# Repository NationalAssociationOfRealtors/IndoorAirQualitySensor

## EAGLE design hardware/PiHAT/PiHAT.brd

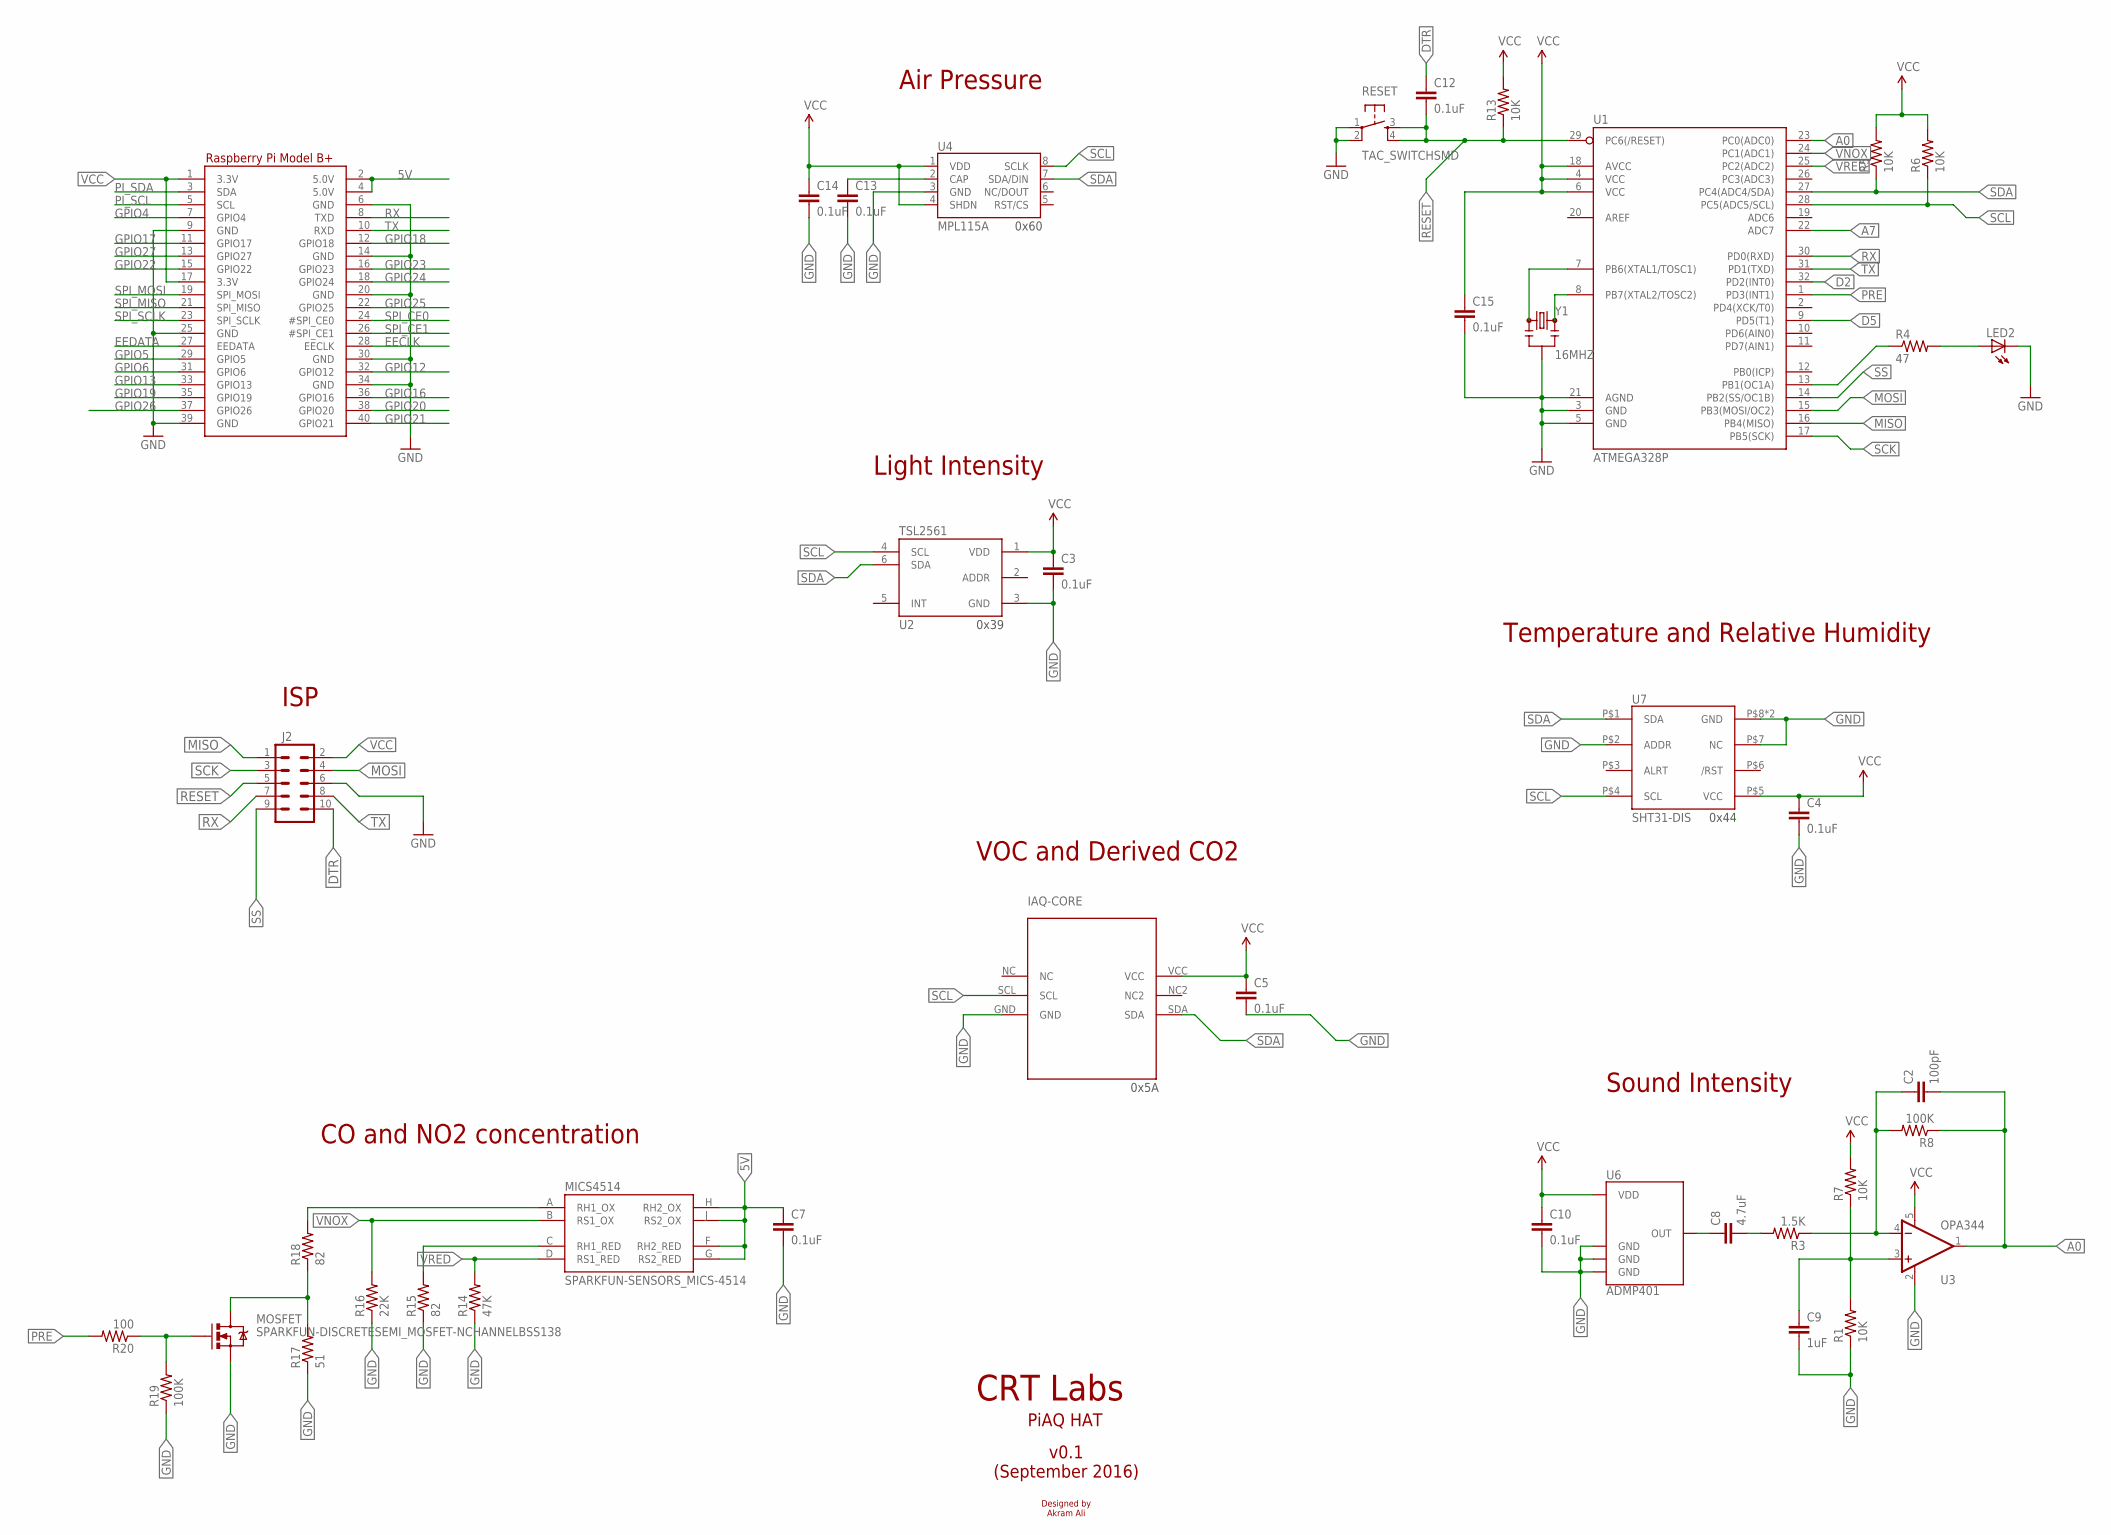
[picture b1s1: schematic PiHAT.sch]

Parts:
C2: 100pF; 0805; DIGIKEY# 311-1111-1-ND
C3, C4, C5, C7, C10, C12, C13, C14, C15: 0.1uF; 0805; DIGIKEY# 311-1088-1-ND
C8: 4.7uF; 0805; DIGIKEY# 311-1871-1-ND
C9: 1uF; 0805; DIGIKEY# 311-1365-1-ND
IAQ-CORE: IAQ-CORE; MPN IAQ CORE; DIGIKEY# IAQ-CORE C-ND
J2: M05X2PTH; AVR_ICSP; DIGIKEY# S6105-ND
LED2: LEDCHIPLED_0805; CHIPLED_0805; DIGIKEY# 475-1196-1-ND
MICS4514: SPARKFUN-SENSORS_MICS-4514; SPARKFUN-SENSORS_MICS_10-SMD
MOSFET: SPARKFUN-DISCRETESEMI_MOSFET-NCHANNELBSS138; SPARKFUN-DISCRETESEMI_SOT23-3
R1, R5, R6, R7, R13: 10K; 0805; DIGIKEY# 311-10KARCT-ND
R3: 1.5K; 0805; DIGIKEY# YAG1814CT-ND
R4: 47; 0805; DIGIKEY# 311-47ARCT-ND
R8: 100K; 0805; DIGIKEY# 541-82.0CCT-ND
R14: 47K; 0805; DIGIKEY# RHM47KKCT-ND
R15, R18: 82; 0805; DIGIKEY# 541-82.0CCT-ND
R16: 22K; 0805; DIGIKEY# 311-22KARCT-ND
R17: 51; 0805; DIGIKEY# RHM51KCT-ND
R19: 100K; 0805; DIGIKEY# 311-100KCRCT-ND
R20: 100; 0805; DIGIKEY# 311-100CRCT-ND
RESET: TAC_SWITCHSMD; TACTILE-SWITCH-SMD; DIGIKEY# CKN9104CT-ND
RPI1: RASPBERRYPI_BPLUS_HATSLOTS; PI_HAT_SLOTS
U1: ATMEGA328P; TQFP32-08; MPN ATMEGA328PB-AU; DIGIKEY# ATMEGA328P-AU-ND
U2: TSL2561; FN-6; MOUSER# 856-TSL2561T; DIGIKEY# TSL2561-FNCT-ND
U3: OPA344; SOT23-5; DIGIKEY# 296-41475-1-ND
U4: MPL115A; LGA8; DIGIKEY# MPL115A2-ND
U6: ADMP401; DIGIKEY# INMP401ACEZ-R7CT-ND
U7: SHT31-DIS; SHT3X; MPN SHT31-DIS-B; DIGIKEY# 1649-1011-1-ND
Y1: 16MHZ; RESONATOR-SMD; DIGIKEY# 490-1198-1-ND

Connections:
5V: C7.1, MICS4514.F (RH2_RED), MICS4514.G (RS2_RED), MICS4514.H (RH2_OX), MICS4514.J (RS2_OX), RPI1.2 (5.0V), RPI1.4 (5.0V)
A0: C2.2, R8.1, U1.23 (PC0(ADC0)), U3.1 (OUT)
A7: U1.22 (ADC7)
D2: U1.32 (PD2(INT0))
D5: U1.9 (PD5(T1))
DTR: C12.1, J2.10
EECLK: RPI1.28 (EECLK)
EEDATA: RPI1.27 (EEDATA)
GND: C3.2, C4.2, C5.2, C7.2, C9.2, C10.2, C13.2, C14.2, C15.2, IAQ-CORE.GND, J2.6, LED2.C, MOSFET.2 (S), R1.1, R14.1, R15.1, R16.1, R17.1, R19.1, RESET.1, RESET.2, RPI1.6 (GND), RPI1.9 (GND), RPI1.14 (GND), RPI1.20 (GND), RPI1.25 (GND), RPI1.30 (GND), RPI1.34 (GND), RPI1.39 (GND), U1.3 (GND), U1.5 (GND), U1.21 (AGND), U2.3 (GND), U3.2 (V-), U4.3 (GND), U6.2 (GND), U6.4 (GND), U6.6 (GND), U7.P$2 (ADDR), U7.P$7 (NC), U7.P$8 (GND), U7.PAD (GND), Y1.2
GPIO4: RPI1.7 (GPIO4)
GPIO5: RPI1.29 (GPIO5)
GPIO6: RPI1.31 (GPIO6)
GPIO12: RPI1.32 (GPIO12)
GPIO13: RPI1.33 (GPIO13)
GPIO16: RPI1.36 (GPIO16)
GPIO17: RPI1.11 (GPIO17)
GPIO18: RPI1.12 (GPIO18)
GPIO19: RPI1.35 (GPIO19)
GPIO20: RPI1.38 (GPIO20)
GPIO21: RPI1.40 (GPIO21)
GPIO22: RPI1.15 (GPIO22)
GPIO23: RPI1.16 (GPIO23)
GPIO24: RPI1.18 (GPIO24)
GPIO25: RPI1.22 (GPIO25)
GPIO26: RPI1.37 (GPIO26)
GPIO27: RPI1.13 (GPIO27)
MISO: J2.1, U1.16 (PB4(MISO))
MOSI: J2.4, U1.15 (PB3(MOSI/OC2))
unnamed: R4.1, U1.13 (PB1(OC1A))
unnamed: LED2.A, R4.2
unnamed: U1.8 (PB7(XTAL2/TOSC2)), Y1.3
unnamed: U1.7 (PB6(XTAL1/TOSC1)), Y1.1
unnamed: C8.1, U6.1 (OUT)
unnamed: MICS4514.A (RH1_OX), R18.2
unnamed: C8.2, R3.2
unnamed: C2.1, R3.1, R8.2, U3.4 (-IN)
unnamed: C9.1, R1.2, R7.1, U3.3 (+IN)
unnamed: C13.1, U4.2 (CAP)
unnamed: MICS4514.C (RH1_RED), R15.2
unnamed: MOSFET.3 (D), R17.2, R18.1
unnamed: MOSFET.1 (G), R19.2, R20.1
PI_SCL: RPI1.5 (SCL)
PI_SDA: RPI1.3 (SDA)
PRE: R20.2, U1.1 (PD3(INT1))
RESET: C12.2, J2.5, R13.1, RESET.3, RESET.4, U1.29 (PC6(/RESET))
RX: J2.7, RPI1.8 (TXD), U1.30 (PD0(RXD))
SCK: J2.3, U1.17 (PB5(SCK))
SCL: IAQ-CORE.SCL, R6.1, U1.28 (PC5(ADC5/SCL)), U2.4 (SCL), U4.8 (SCLK), U7.P$4 (SCL)
SDA: IAQ-CORE.SDA, R5.1, U1.27 (PC4(ADC4/SDA)), U2.6 (SDA), U4.7 (SDA/DIN), U7.P$1 (SDA)
SPI_CE0: RPI1.24 (#SPI_CE0)
SPI_CE1: RPI1.26 (#SPI_CE1)
SPI_MISO: RPI1.21 (SPI_MISO)
SPI_MOSI: RPI1.19 (SPI_MOSI)
SPI_SCLK: RPI1.23 (SPI_SCLK)
SS: J2.9, U1.14 (PB2(SS/OC1B))
TX: J2.8, RPI1.10 (RXD), U1.31 (PD1(TXD))
VCC: C3.1, C4.1, C5.1, C10.1, C14.1, C15.1, IAQ-CORE.VCC, J2.2, R5.2, R6.2, R7.2, R13.2, RPI1.1 (3.3V), RPI1.17 (3.3V), U1.4 (VCC), U1.6 (VCC), U1.18 (AVCC), U2.1 (VDD), U3.5 (V+), U4.1 (VDD), U4.4 (SHDN), U6.5 (VDD), U7.P$5 (VCC)
VNOX: MICS4514.B (RS1_OX), R16.2, U1.24 (PC1(ADC1))
VRED: MICS4514.D (RS1_RED), R14.2, U1.25 (PC2(ADC2))

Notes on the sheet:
Light Intensity
VOC and Derived CO2
Air Pressure
Sound Intensity
Temperature and Relative Humidity
ISP
CO and NO2 concentration
CRT Labs
PiAQ HAT
v0.1 (September 2016)
Designed by Akram Ali
0x39
0x60
0x5A
0x44

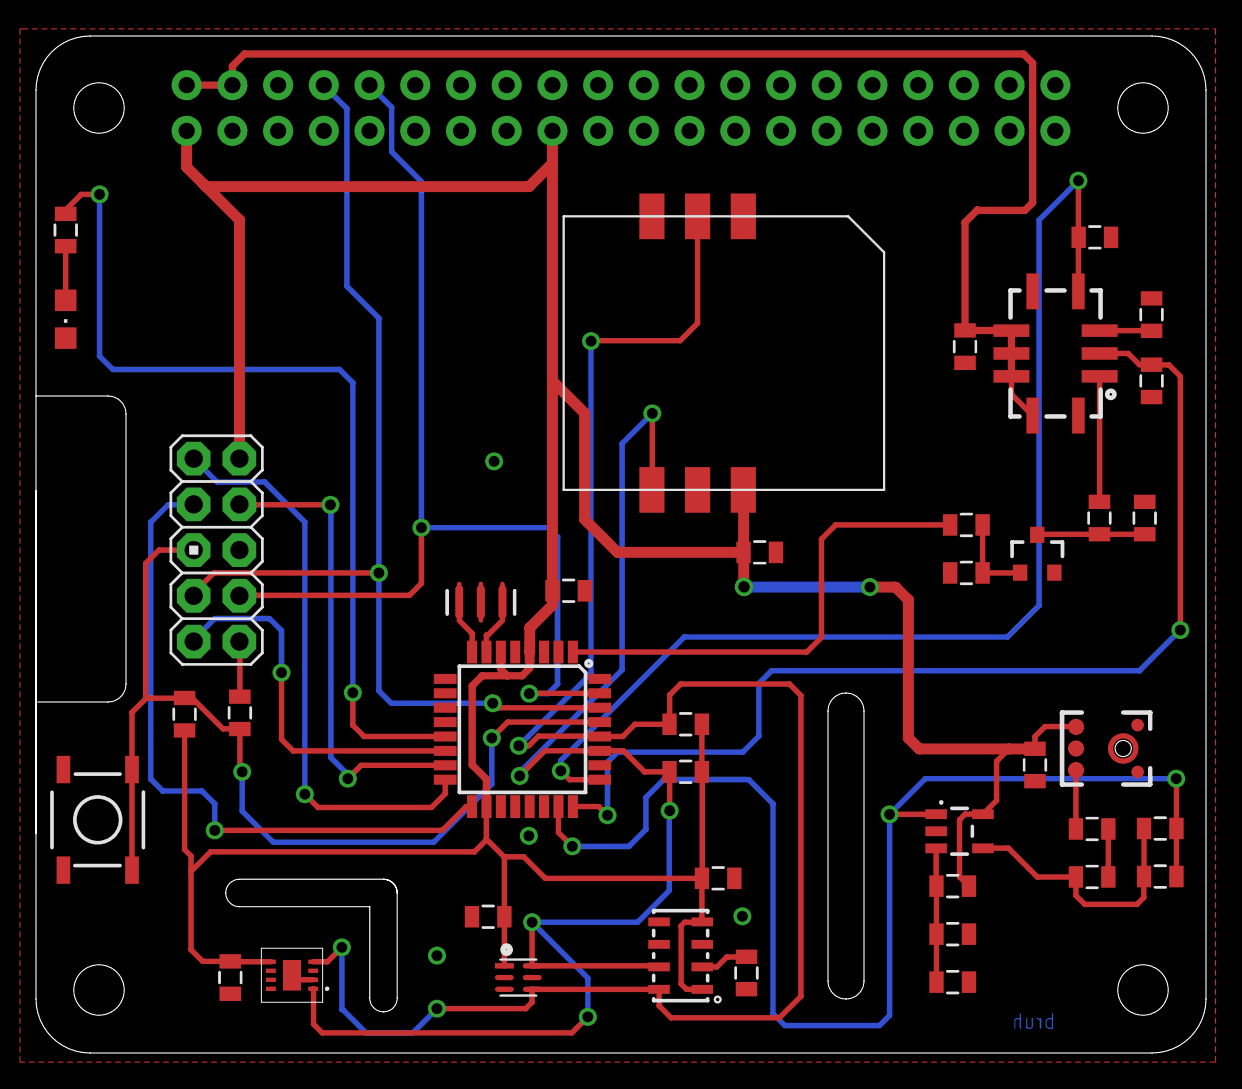
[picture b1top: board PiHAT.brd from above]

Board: 2 copper layers, 65.0 x 56.5 mm, 41 parts (0 on the bottom side), 30 nets.

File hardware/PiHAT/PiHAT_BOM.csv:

Qty,Value,Device,Package,Parts,Description,DIGIKEY#,MANF,MANF#,MF,MOUSER#,MPN,OC_NEWARK,PROD_ID,VALUE
1,,LEDCHIPLED_0805,CHIPLED_0805,LED2,LED,475-1196-1-ND,,,,,,unknown,,
1,,M05X2PTH,AVR_ICSP,J2,Header 5x2,,,,,,,,,
9,0.1uF,CAP0805,805,C3,,311-1088-1-ND,,,,,,,,
1,1.5K,RESISTOR0805-RES,805,R3,Resistor,YAG1814CT-ND,,,,,,,,
1,100,RESISTOR0805-RES,805,R20,Resistor,311-100CRCT-ND,,,,,,,,
1,100K,RESISTOR0805-RES,805,R19,Resistor,311-100KCRCT-ND,,,,,,,,
1,100K,RESISTOR0805-RES,805,R8,Resistor,541-82.0CCT-ND,,,,,,,,
1,100pF,CAP0805,805,C2,Capacitor,311-1111-1-ND,,,,,,,,
5,10K,RESISTOR0805-RES,805,R1,,,,,,,,,,
1,16MHZ,RESONATOR16MHZ,RESONATOR-SMD,Y1,Resonator,490-1198-1-ND,,,,,,unknown,XTAL-08900,16MHZ
1,1uF,CAP0805,805,C9,Capacitor,311-1365-1-ND,,,,,,,,
1,22K,RESISTOR0805-RES,805,R16,Resistor,311-22KARCT-ND,,,,,,unknown,,
1,4.7uF,CAP0805,805,C8,Capacitor,311-1871-1-ND,,,,,,,,
1,47,RESISTOR0805-RES,805,R4,Resistor,311-47ARCT-ND,,,,,,unknown,,
1,47K,RESISTOR0805-RES,805,R14,Resistor,RHM47KKCT-ND,,,,,,unknown,,
1,51,RESISTOR0805-RES,805,R17,Resistor,RHM51KCT-ND,,,,,,,,
2,82,RESISTOR0805-RES,805,R15,,541-82.0CCT-ND,,,,,,,,
1,ADMP401,ADMP401,ADMP401,U6,Omnidirection bottom-port MEMS microphone,INMP401ACEZ-R7CT-ND,,,,,,,,
1,ATMEGA328P,ATMEGA328P_TQFP,TQFP32-08,U1,,ATMEGA328P-AU-ND,,,,,ATMEGA328PB-AU,58Y6083,IC-09069,ATMEGA328P_TQFP
1,IAQ-CORE,IAQ-CORE,IAQ-CORE,IAQ-CORE,,IAQ-CORE C-ND,,,,,IAQ CORE,82Y5455,,
1,MPL115A,MPL115A,LGA8,U4,MPL115A1 (SPI) and MPL115A2 (I2C) Miniature Digital Barometer,MPL115A2-ND,,,,,,,,
1,OPA344,OPA344,SOT23-5,U3,Single gate rail-to-rail output op-amp. Inputs extend 300mV past rails.,296-41475-1-ND,,,,,,,IC-08251,
1,RASPBERRYPI_BPLUS_HATSLOTS,RASPBERRYPI_BPLUS_HATSLOTS,PI_HAT_SLOTS,RPI1,,,,,,,,,,
1,SHT31-DIS,SHT31-DIS,SHT3X,U7,,1649-1011-1-ND,,,,,SHT31-DIS-B,47Y1304,,
1,SPARKFUN-DISCRETESEMI_MOSFET-NCHANNELBSS138,SPARKFUN-DISCRETESEMI_MOSFET-NCHANNELBSS138,SPARKFUN-DISCRETESEMI_SOT23-3,MOSFET,Common NMOSFET Parts,,,,,,,,TRANS-00830,
1,SPARKFUN-SENSORS_MICS-4514,SPARKFUN-SENSORS_MICS-4514,SPARKFUN-SENSORS_MICS_10-SMD,MICS4514,Metal oxide MEMS carbon monoxide (CO) and NOx sensor in an SMD package.,,,,,,,,COMP-12310,
1,TAC_SWITCHSMD,TAC_SWITCHSMD,TACTILE-SWITCH-SMD,RESET,Momentary Switch,CKN9104CT-ND,,,,,,,SWCH-08247,TAC_SWITCHSMD
1,TSL2561,TSL2561FN,FN-6,U2,TSL2561 illumination sensor,TSL2561-FNCT-ND,AMS-TAOS-USA-Inc.,TSL2561FN,,856-TSL2561T,TSL2561FN,82Y5564,IC-11791,

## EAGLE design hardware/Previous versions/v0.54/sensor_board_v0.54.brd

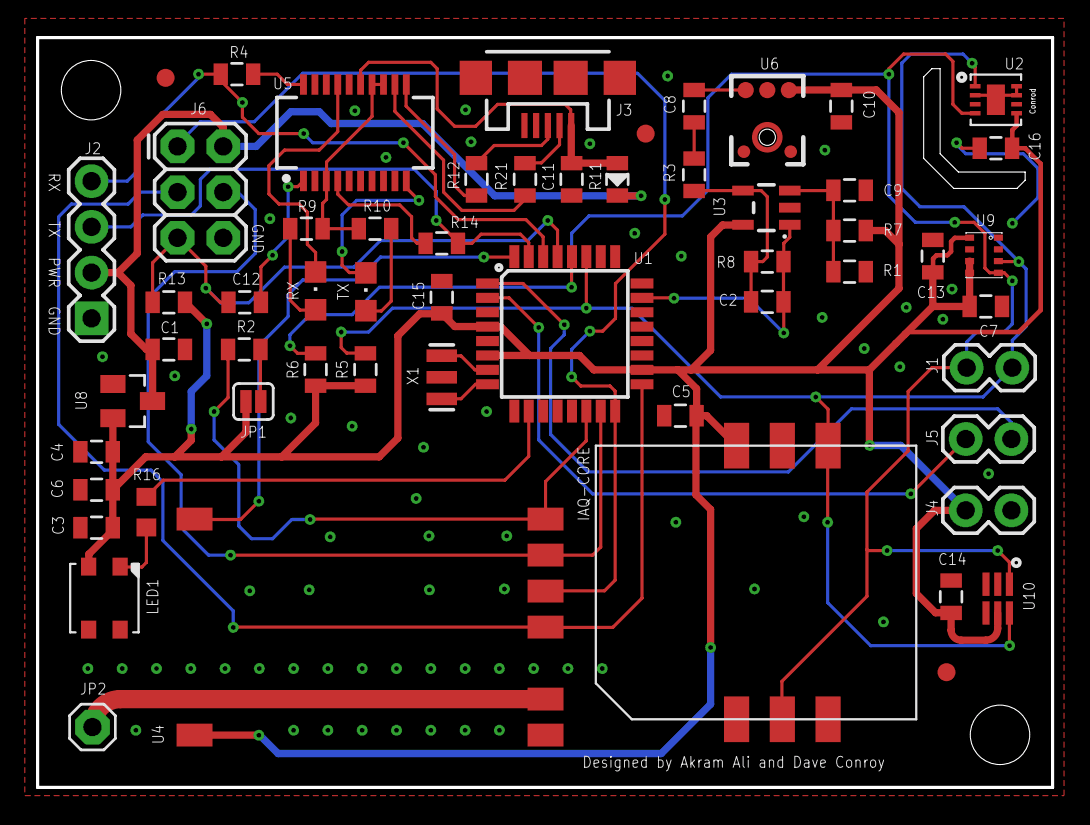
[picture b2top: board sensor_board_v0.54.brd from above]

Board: 2 copper layers, 56.4 x 41.7 mm, 59 parts (0 on the bottom side), 39 nets.

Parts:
C1, C3, C9: 1uF; 0805
C2: 100pF; 0805
C4: 10uF; 0805
C5, C6, C7, C10, C11, C12, C13, C14, C15, C16: 0.1uF; 0805
C8: 4.7uF; 0805
H1, H2: STAND-OFF
IAQ-CORE: IAQ-CORE
J1, J4, J5: 1X02
J2: 1X04
J3: USB-MICROB
J6: AVR_SPI_PRG_6PTH; 2X3
JP1: JUMPER-PAD-2-NC_BY_PASTEFULL-BOX-SILK; PAD-JUMPER-2-NC_BY_PASTE_YES_SILK_FULL_BOX
JP2: 1X01
LED1: WS2812B3535; LED3535
R1, R2, R5, R6, R7, R13: 10K; 0805
R3: 1.5K; 0805
R4, R14: 1K; 0805
R8: 100K; 0805
R9, R10: 47; 0805
R11: SHOTTKY; 0805
R12, R21: 27; 0805
R16: 470; R0603
RX: CHIPLED_0805
TX: CHIPLED_0805
U1: ATMEGA328P; TQFP32-08
U2: SHT35; SHT3X
U3: OPA344; SOT23-5
U4: RFM69HW; LOWPOWERLAB_RFM69W-MINPADS
U5: FT231XS; SSOP20_L
U6: ADMP401
U8: MCP1703CB; SOT23
U9: BMP280
U10: TSL2591; DFN6_TAOS
U$1, U$2, U$3: FIDUCIAL; FIDUCIAL_1MM
X1: 16 MHz; RESONATOR-SMD

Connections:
A0: C2.2, R8.1, U1.23, U3.1
ANT: JP2.1, U4.ANA
D2: U1.32, U4.DIO0
D3: J5.2, U1.1
D4: J5.1, U1.2
D6: R16.2, U1.10
DTR: C12.1, U5.1
FTDI_VCC: R9.1, R10.1, U5.3, U5.13, U5.14
GND: C1.2, C3.2, C4.2, C5.2, C6.2, C7.2, C9.2, C10.2, C11.2, C13.2, C14.1, C15.2, C16.2, IAQ-CORE.GND, J2.1, J3.GND, J3.MT1, J3.MT2, J4.1, J6.6, LED1.4, R1.1, U1.3, U1.5, U1.21, U2.2, U2.7, U2.8, U2.THERMAL, U3.2, U4.GND, U5.6, U5.16, U6.2, U6.4, U6.6, U8.1, U9.1, U9.7, U10.3, X1.2
MISO: J6.1, U1.16, U4.MISO
MOSI: J6.4, U1.15, U4.MOSI
unnamed: JP1.1, R2.2
unnamed: R14.2, U5.4
unnamed: R4.2, U5.20
unnamed: U1.8, X1.3
unnamed: U1.7, X1.1
unnamed: LED1.1, R16.1
unnamed: C8.2, R3.2
unnamed: C2.1, R3.1, R8.2, U3.4
unnamed: C9.1, R1.2, R7.1, U3.3
unnamed: RX.C, U5.17
unnamed: TX.C, U5.10
unnamed: R21.1, U5.12
unnamed: R12.1, U5.11
unnamed: R9.2, RX.A
unnamed: R10.2, TX.A
unnamed: J3.D-, R21.2
unnamed: J3.D+, R12.2
OUT: C8.1, U6.1
PWR: C1.1, J2.2, J6.2, R11.1, U8.3
RESET: C12.2, J6.5, R13.1, U1.29
RX: J2.4, R4.1, U1.30
SCK: J6.3, U1.17, U4.SCK
SCL: IAQ-CORE.SCL, J1.1, R6.1, U1.28, U2.4, U9.4, U10.1
SDA: IAQ-CORE.SDA, J1.2, R5.1, U1.27, U2.1, U9.3, U10.6
SS: R2.1, U1.14, U4.NSS
TX: J2.3, R14.1, U1.31
VBUS: C11.1, J3.VBUS, R11.2, U5.15
VCC: C3.1, C4.1, C5.1, C6.1, C7.1, C10.1, C13.1, C14.2, C15.1, C16.1, IAQ-CORE.VCC, J4.2, JP1.2, LED1.2, R5.2, R6.2, R7.2, R13.2, U1.4, U1.6, U1.18, U2.5, U3.5, U4.VDD, U6.5, U8.2, U9.5, U9.6, U9.8, U10.5

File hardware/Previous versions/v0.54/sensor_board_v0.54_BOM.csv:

Qty,Value,Device,Package,Parts,Description,MPN
1,USB-MICROB,USB-MICROB,USB-MICROB,J3,USB Connectors,47346-0001
1,ATMEGA328P,ATMEGA328P_TQFP,TQFP32-08,U1,ATMEGA328P,ATMEGA328PB-AU
1,BMP280,BMP280,BMP280,U9,The BMP280 is an absolute barometric pressure sensor especially designed for mobile applications. The sensor module is housed in an extremely compact 8-pin metal-lid LGA package with a footprint of only 2.0 ÌÑ 2.5 mm2 and 0.95 mm package height. Its small,BMP280
1,100pF,CAP0805,805,C2,Capacitor,CC0805JRNPOABN101
1,10uF,CAP0805,805,C4,Capacitor,CC0805KKX5R6BB106
1,4.7uF,CAP0805,805,C8,Capacitor,CC0805KKX7R6BB475
10,0.1uF,CAP0805,805,C5-C6-C7-C10-C11-C12-C13-C14-C15-C16,Capacitor,CC0805KRX7R9BB104
3,1uF,CAP0805,805,C1-C3-C9,Capacitor,CC0805ZRY5V8BB105
1,16MHZ,RESONATOR16MHZ,RESONATOR-SMD,Y1,Resonator,CSTCE16M0V53-R0
1,FT231XS,FT231XS,SSOP20_L,U5,FTDI FT231X Full Speed USB to Full-handshake UART,FT231XQ-R
1,IAQ-CORE,IAQ-CORE,IAQ-CORE,IAQ-CORE,IAQ-CORE,IAQ-CORE C
1,ADMP401,ADMP401,ADMP401,U6,Omnidirection bottom-port MEMS microphone,INMP401ACEZ-R7
2,,LEDCHIPLED_0805,CHIPLED_0805,RX- TX,LED,LG R971-KN-1
1,MCP1703CB,MCP1703CB,SOT23,U8,250 mA- 16V- Low Quiescent Current LDO Regulator,MCP1703T-2502E/CB
1,OPA344,OPA344,SOT23-5,U3,Single gate rail-to-rail output op-amp. Inputs extend 300mV past rails.,OPA344NA/3K
1,100K,RESISTOR0805-RES,805,R8,Resistor,RC0805FR-07100KL 
6,10K,RESISTOR0805-RES,805,R1-R2-R5-R6-R7-R13,Resistor,RC0805FR-0710KL
1,1.5K,RESISTOR0805-RES,805,R3,Resistor,RC0805FR-071K5L 
2,1K,RESISTOR0805-RES,805,R4-R14,Resistor,RC0805FR-071KL
2,27,RESISTOR0805-RES,805,R12-R21,Resistor,RC0805FR-0727RL 
1,470,R-US_R0603,R0603,R16,RESISTOR- American symbol,RC0805FR-07470RL 
2,47,RESISTOR0805-RES,805,R9-R10,Resistor,RC0805FR-0747RL 
1,RFM69HW,LOWPOWERLAB_RFM69,LOWPOWERLAB_RFM69W-MINPADS,U4,RFM Radio,RFM69HW
1,SHOTTKY,RESISTOR0805-RES,805,R11,Resistor,SD0805S040S0R5
1,SHT35,SHT3X,SHT3X,U2,SHT3x - Digital Temperature and Humidity Sensor,SHT35-DIS-B
1,WS2812B3535,WS2812B3535,LED3535,LED1,LED,SK6812 mini
1,TSL2591,LIGHT_TSL2591,DFN6_TAOS,U10,TSL2591 Light-To-Digital Sensor,TSL25911FN

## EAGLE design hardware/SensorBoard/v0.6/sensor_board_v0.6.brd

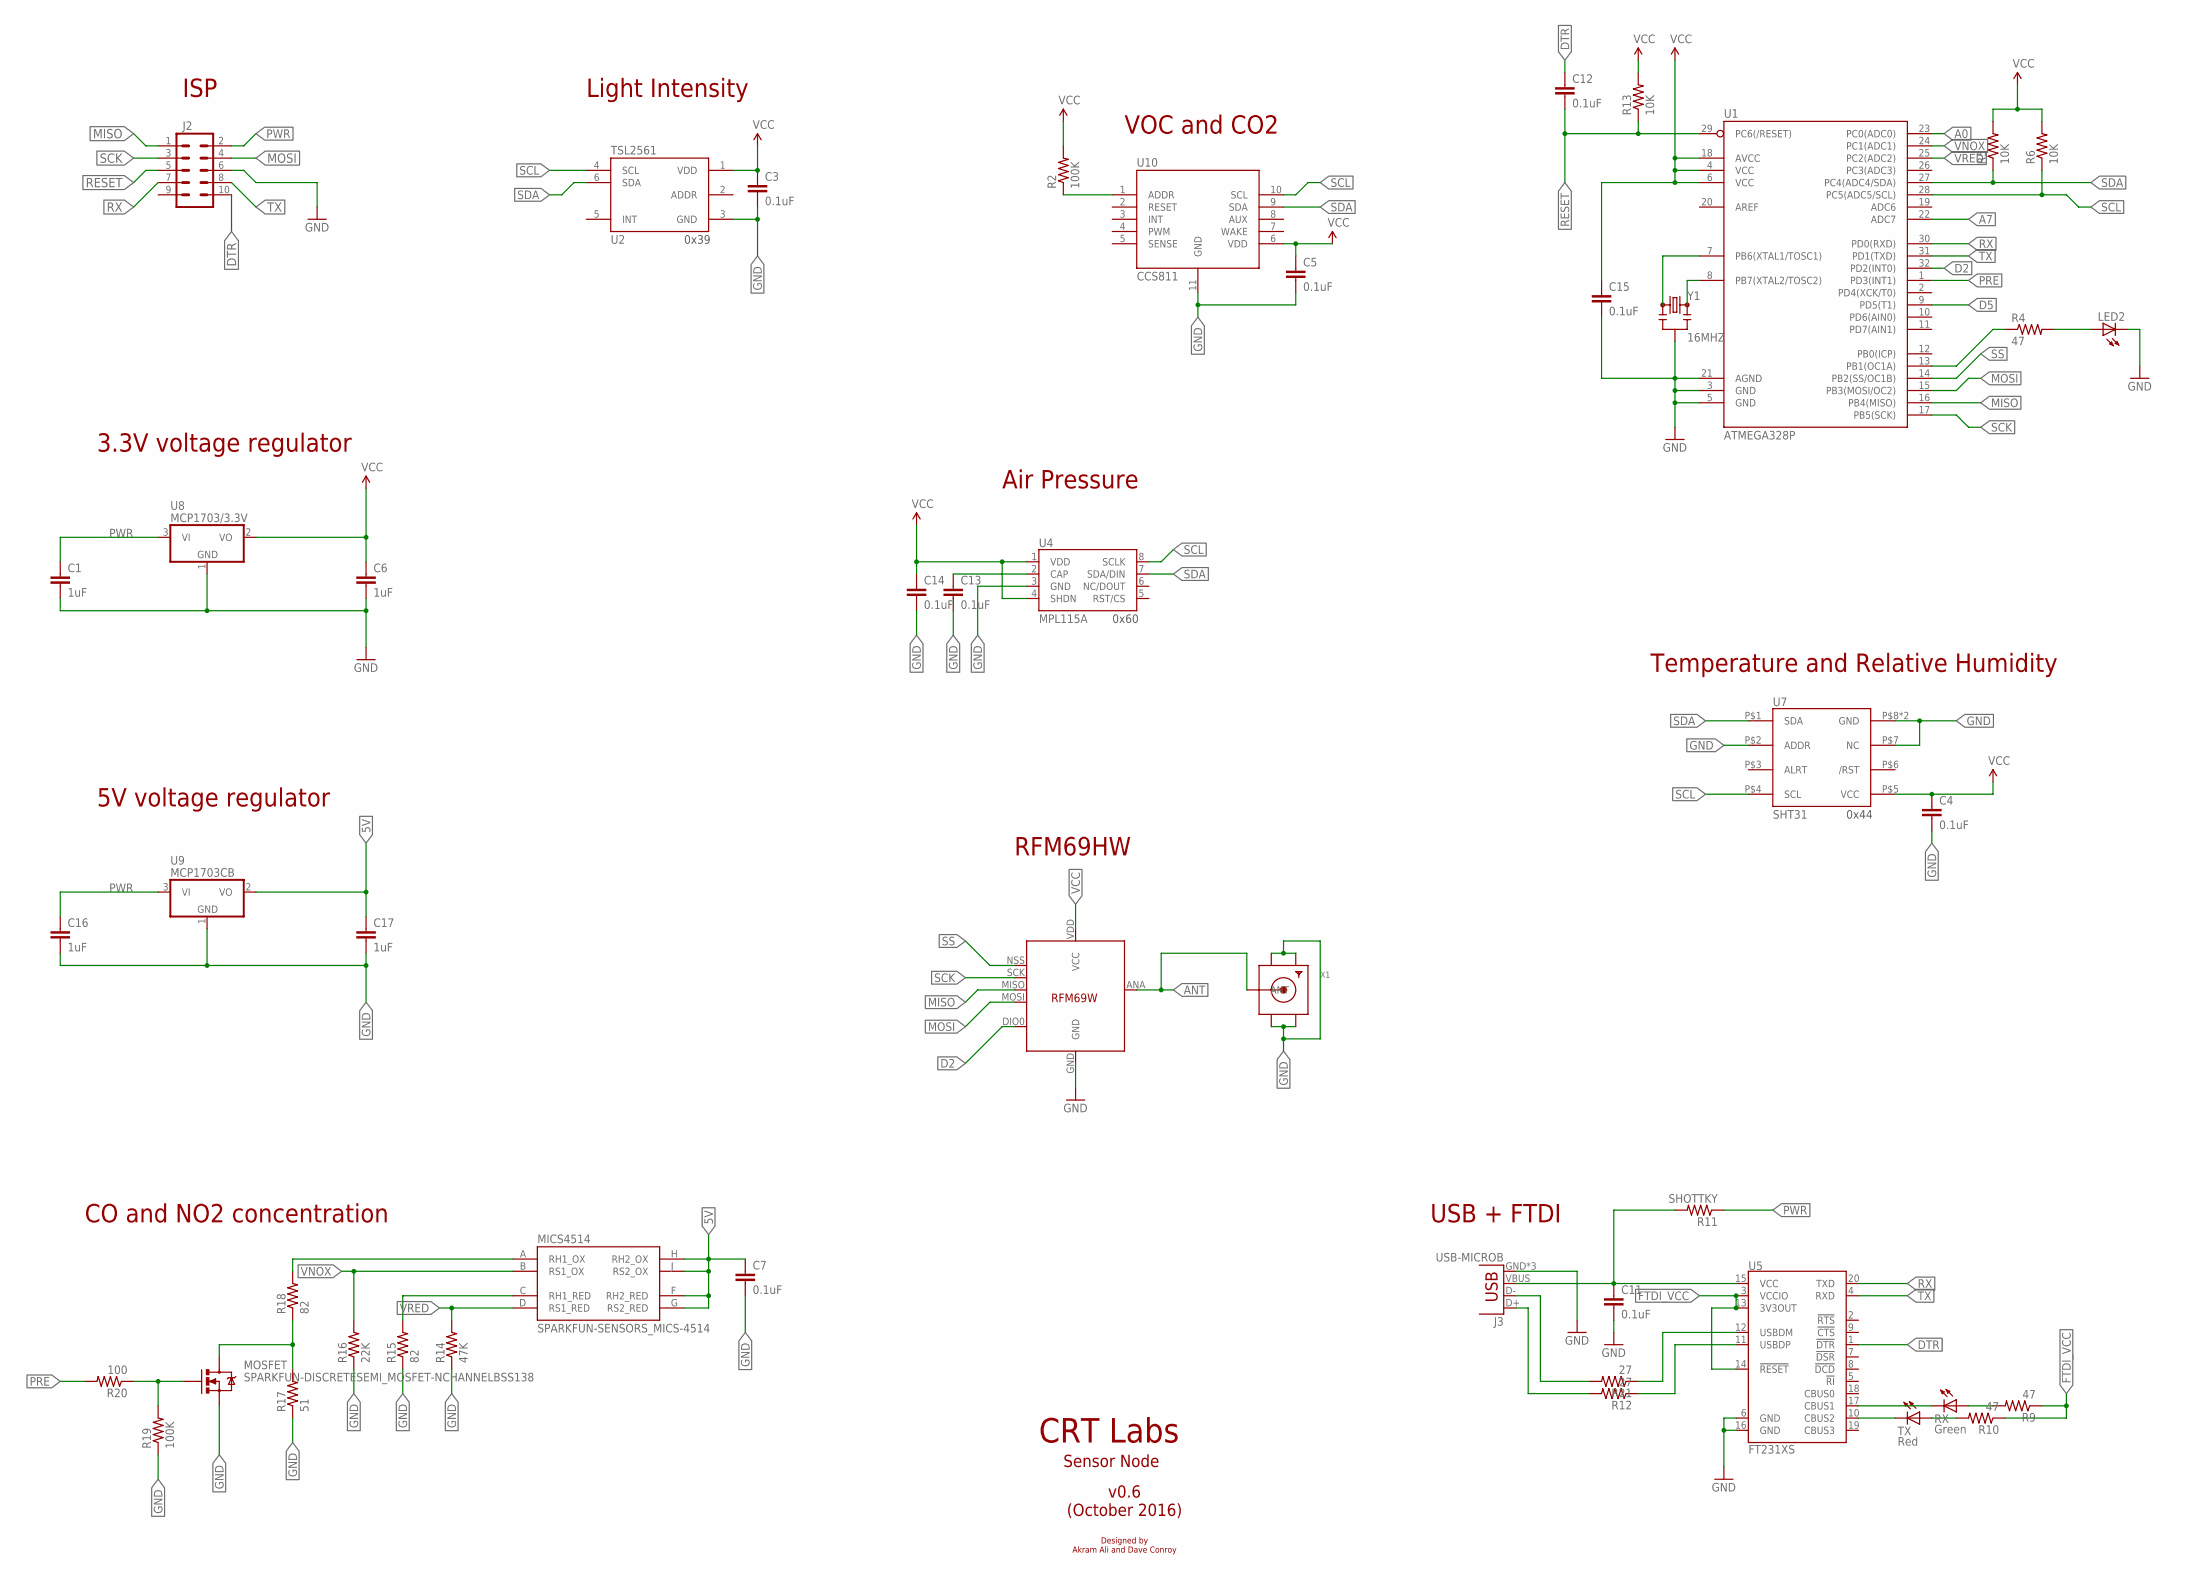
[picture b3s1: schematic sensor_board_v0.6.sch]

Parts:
C1, C6, C16, C17: 1uF; 0805
C3, C4, C5, C7, C11, C12, C13, C14, C15: 0.1uF; 0805
J2: M05X2PTH; AVR_ICSP
J3: USB-MICROB
LED2: LEDCHIPLED_0805; CHIPLED_0805
MICS4514: SPARKFUN-SENSORS_MICS-4514; SPARKFUN-SENSORS_MICS_10-SMD
MOSFET: SPARKFUN-DISCRETESEMI_MOSFET-NCHANNELBSS138; SPARKFUN-DISCRETESEMI_SOT23-3
R2, R19: 100K; 0805
R4, R9, R10: 47; 0805
R5, R6, R13: 10K; 0805
R11: SHOTTKY; 0805
R12, R21: 27; 0805
R14: 47K; 0805
R15, R18: 82; 0805
R16: 22K; 0805
R17: 51; 0805
R20: 100; 0805
RX: Green; CHIPLED_0805
TX: Red; CHIPLED_0805
U1: ATMEGA328P; TQFP32-08; MPN ATMEGA328PB-AU
U2: TSL2561; FN-6; MOUSER# 856-TSL2561T; DIGIKEY# TSL2561-FNCT-ND
U4: MPL115A; LGA8
U5: FT231XS; SSOP20_L
U7: SHT31; SHT3X; MPN SHT31-DIS-B
U8: MCP1703/3.3V; SOT23; MPN MCP1703T-2502E/CB
U9: MCP1703CB; SOT23; MPN MCP1703T-2502E/CB
U10: CCS811; LGA
U11: RFM69HW; LOWPOWERLAB_RFM69W-MINPADS
X1: SMACONNECTOR_EDGE; SMA_EDGELAUNCH
Y1: 16MHZ; RESONATOR-SMD

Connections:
5V: C7.1, C17.1, MICS4514.F (RH2_RED), MICS4514.G (RS2_RED), MICS4514.H (RH2_OX), MICS4514.J (RS2_OX), U9.2 (VO)
A0: U1.23 (PC0(ADC0))
A7: U1.22 (ADC7)
ANT: U11.ANA (ANT), X1.P (ANT)
D2: U1.32 (PD2(INT0)), U11.DIO0
D5: U1.9 (PD5(T1))
DTR: C12.1, J2.10, U5.1 (!DTR)
FTDI_VCC: R9.1, R10.1, U5.3 (VCCIO), U5.13 (3V3OUT), U5.14 (!RESET)
GND: C1.2, C3.2, C4.2, C5.2, C6.2, C7.2, C11.2, C13.2, C14.2, C15.2, C16.2, C17.2, J2.6, J3.GND, J3.MT1 (GND), J3.MT2 (GND), LED2.C, MOSFET.2 (S), R14.1, R15.1, R16.1, R17.1, R19.1, U1.3 (GND), U1.5 (GND), U1.21 (AGND), U2.3 (GND), U4.3 (GND), U5.6 (GND), U5.16 (GND), U7.P$2 (ADDR), U7.P$7 (NC), U7.P$8 (GND), U7.PAD (GND), U8.1 (GND), U9.1 (GND), U10.11 (GND), U11.GND, X1.GND@1 (GND4), X1.GND@2 (GND3), X1.GND@3 (GND2), X1.GND@4 (GND1), Y1.2
MISO: J2.1, U1.16 (PB4(MISO)), U11.MISO
MOSI: J2.4, U1.15 (PB3(MOSI/OC2)), U11.MOSI
unnamed: R2.1, U10.1 (ADDR)
unnamed: R4.1, U1.13 (PB1(OC1A))
unnamed: LED2.A, R4.2
unnamed: U1.8 (PB7(XTAL2/TOSC2)), Y1.3
unnamed: U1.7 (PB6(XTAL1/TOSC1)), Y1.1
unnamed: MICS4514.A (RH1_OX), R18.2
unnamed: C13.1, U4.2 (CAP)
unnamed: MICS4514.C (RH1_RED), R15.2
unnamed: RX.C, U5.17 (CBUS1)
unnamed: TX.C, U5.10 (CBUS2)
unnamed: MOSFET.3 (D), R17.2, R18.1
unnamed: MOSFET.1 (G), R19.2, R20.1
unnamed: R21.1, U5.12 (USBDM)
unnamed: R12.1, U5.11 (USBDP)
unnamed: R9.2, RX.A
unnamed: R10.2, TX.A
unnamed: J3.D-, R21.2
unnamed: J3.D+, R12.2
PRE: R20.2, U1.1 (PD3(INT1))
PWR: C1.1, C16.1, J2.2, R11.1, U8.3 (VI), U9.3 (VI)
RESET: C12.2, J2.5, R13.1, U1.29 (PC6(/RESET))
RX: J2.7, U1.30 (PD0(RXD)), U5.20 (TXD)
SCK: J2.3, U1.17 (PB5(SCK)), U11.SCK
SCL: R6.1, U1.28 (PC5(ADC5/SCL)), U2.4 (SCL), U4.8 (SCLK), U7.P$4 (SCL), U10.10 (SCL)
SDA: R5.1, U1.27 (PC4(ADC4/SDA)), U2.6 (SDA), U4.7 (SDA/DIN), U7.P$1 (SDA), U10.9 (SDA)
SS: U1.14 (PB2(SS/OC1B)), U11.NSS (SEL)
TX: J2.8, U1.31 (PD1(TXD)), U5.4 (RXD)
VBUS: C11.1, J3.VBUS, R11.2, U5.15 (VCC)
VCC: C3.1, C4.1, C5.1, C6.1, C14.1, C15.1, R2.2, R5.2, R6.2, R13.2, U1.4 (VCC), U1.6 (VCC), U1.18 (AVCC), U2.1 (VDD), U4.1 (VDD), U4.4 (SHDN), U7.P$5 (VCC), U8.2 (VO), U10.6 (VDD), U11.VDD (VCC)
VNOX: MICS4514.B (RS1_OX), R16.2, U1.24 (PC1(ADC1))
VRED: MICS4514.D (RS1_RED), R14.2, U1.25 (PC2(ADC2))

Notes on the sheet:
Light Intensity
VOC and CO2
Air Pressure
Temperature and Relative Humidity
ISP
3.3V voltage regulator
CO and NO2 concentration
CRT Labs
Sensor Node
v0.6 (October 2016)
Designed by Akram Ali and Dave Conroy
5V voltage regulator
RFM69HW
USB + FTDI
0x39
0x60
0x44

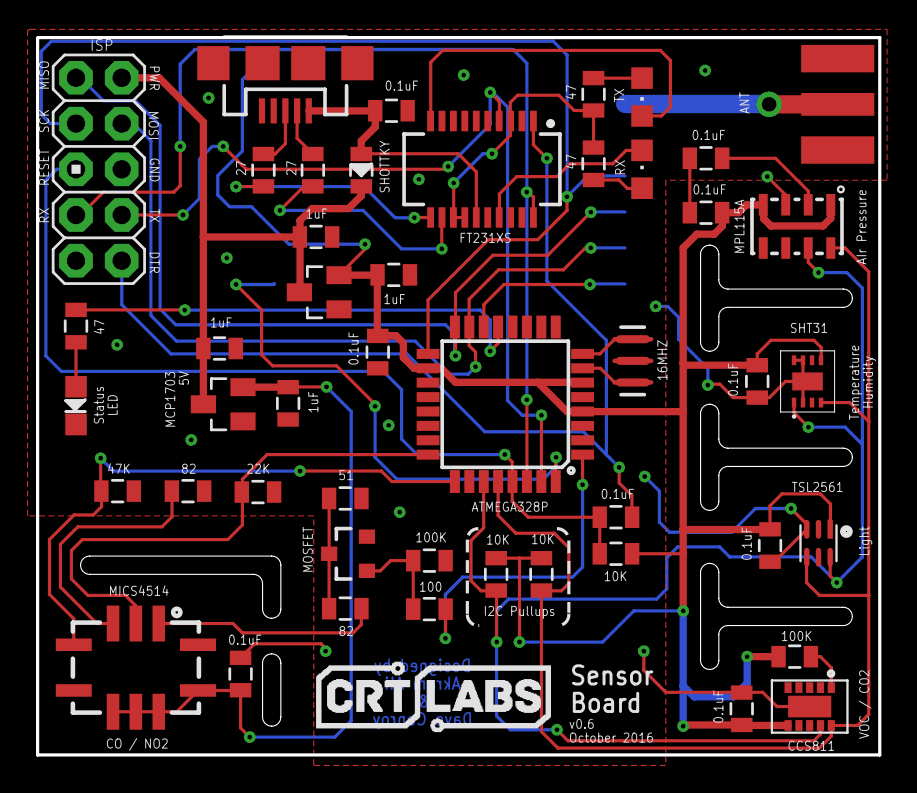
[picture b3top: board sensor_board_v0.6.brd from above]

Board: 2 copper layers, 46.8 x 39.9 mm, 48 parts (1 on the bottom side), 39 nets.

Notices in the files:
parts and their libraries:
microbuilder: This work is placed in the public domain, and may be freely used for commercial and non-commercial work with the following conditions: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
SparkFun-DigitalIC: Licensing: Creative Commons ShareAlike 4.0 International - https://creativecommons.org/licenses/by-sa/4.0
